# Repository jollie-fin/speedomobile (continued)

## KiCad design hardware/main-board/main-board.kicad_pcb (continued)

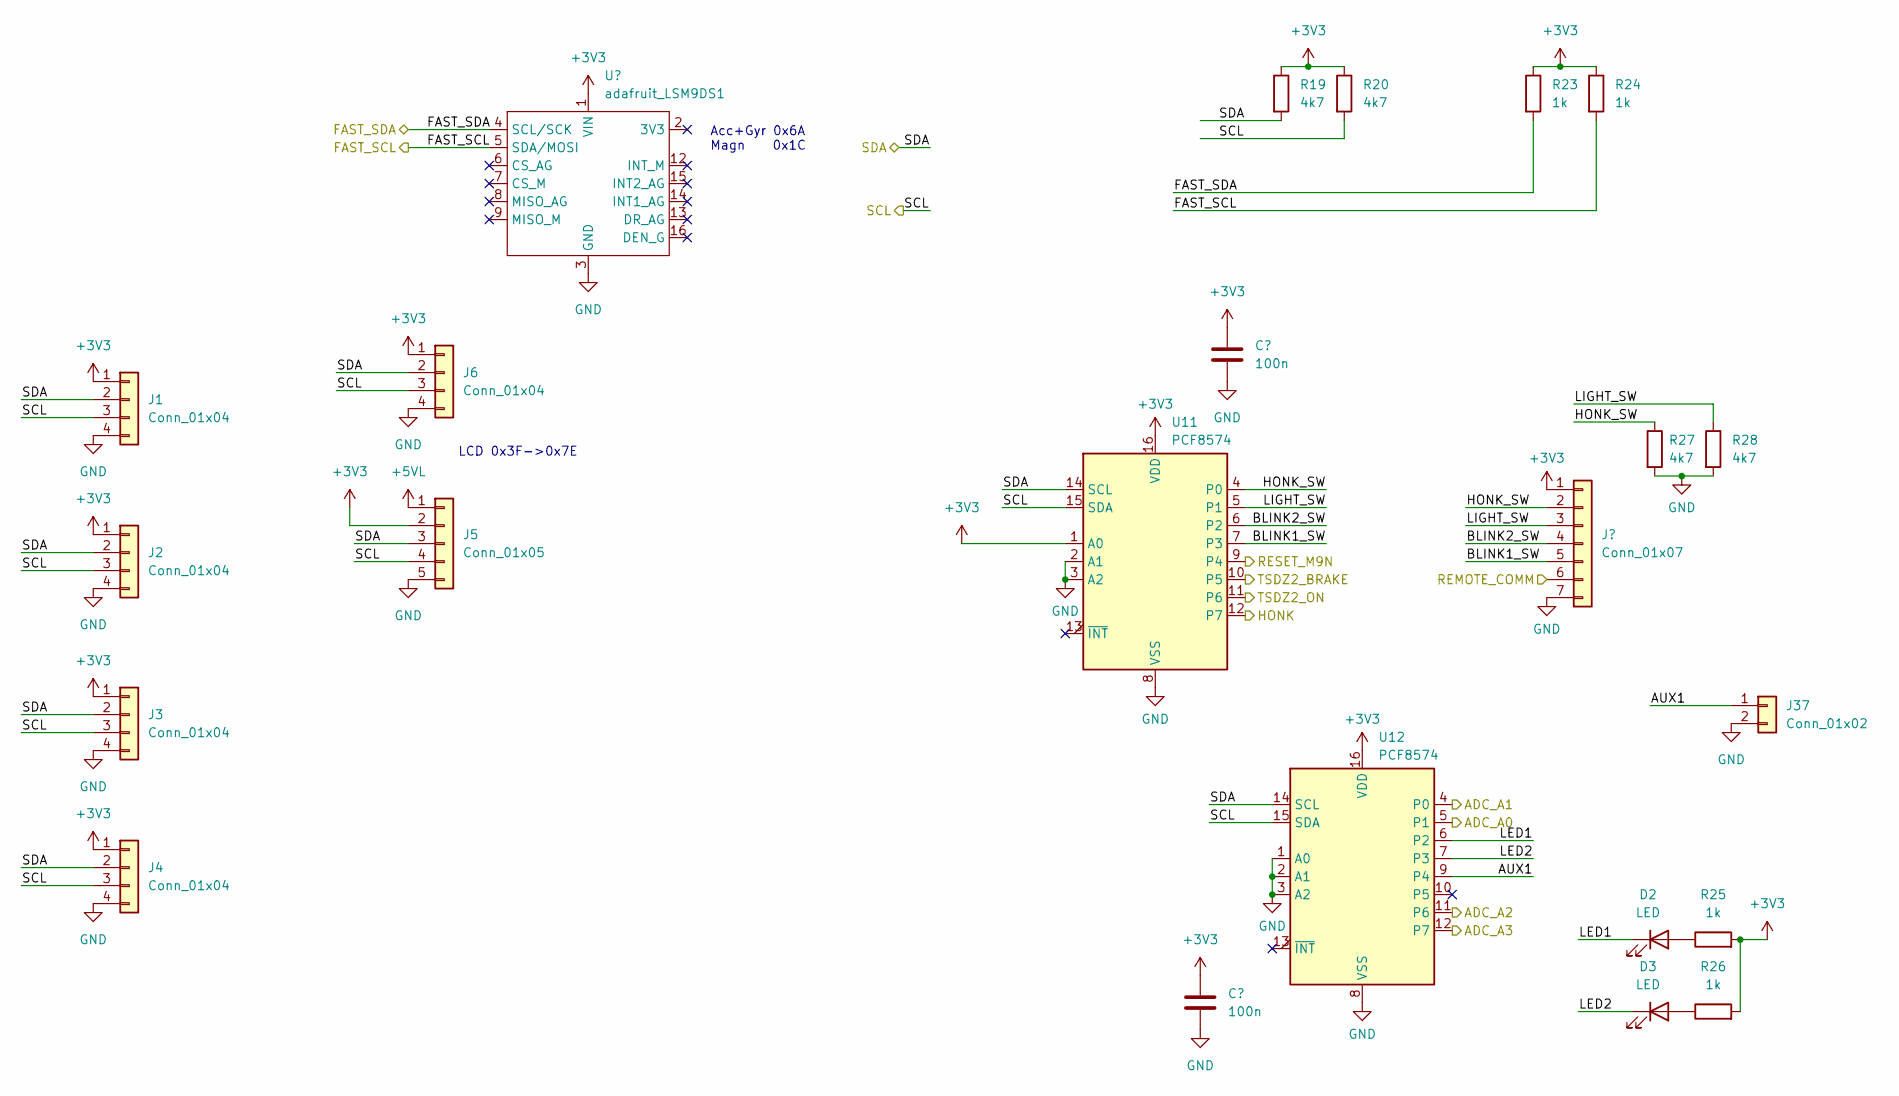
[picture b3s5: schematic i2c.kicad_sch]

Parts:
C21, C22: 100n; C_1206_3216Metric; mouser 80-C1206C104K5R
D2: LED; LED_1206_3216Metric; mouser 710-156120RS75300
D3: LED; LED_1206_3216Metric; mouser 710-156120VS75000
J1, J2, J3, J4, J6: Conn_01x04; JST_XH_B4B-XH-A_1x04_P2.50mm_Vertical
J5: Conn_01x05; JST_XH_B5B-XH-A_1x05_P2.50mm_Vertical
J7: Conn_01x07; JST_XH_B7B-XH-A_1x07_P2.50mm_Vertical
J37: Conn_01x02; JST_XH_B2B-XH-A_1x02_P2.50mm_Vertical
R19, R20, R27, R28: 4k7; R_1206_3216Metric; mouser 791-WR12X4701FTL
R23, R24, R25, R26: 1k; R_1206_3216Metric; mouser 603-AC1206FR-101KL
U9: adafruit_LSM9DS1; lsm9ds1_wo_holes
U11, U12: PCF8574; SOIC-16W_7.5x10.3mm_P1.27mm; mouser 771-PCF8574ATD-T

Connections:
+3V3: C21.1, C22.1, J1.1, J2.1, J3.1, J4.1, J5.2, J6.1, J7.1, R19.1, R20.1, R23.1, R24.1, R25.2, R26.2, U9.1 (VIN), U11.1 (A0), U11.16 (VDD), U12.16 (VDD); also elsewhere on the board
+5VL: J5.1; also elsewhere on the board
/ADC_A0: U12.5 (P1); also elsewhere on the board
/ADC_A1: U12.4 (P0); also elsewhere on the board
/ADC_A2: U12.11 (P6); also elsewhere on the board
/ADC_A3: U12.12 (P7); also elsewhere on the board
/FAST_SCL: R24.2, U9.5 (SDA/MOSI); also elsewhere on the board
/FAST_SDA: R23.2, U9.4 (SCL/SCK); also elsewhere on the board
/HONK: U11.12 (P7); also elsewhere on the board
/I2C devices/AUX1: J37.1, U12.9 (P4)
/I2C devices/LED1: D2.1 (K), U12.6 (P2)
/I2C devices/LED2: D3.1 (K), U12.7 (P3)
/RESET_M9N: U11.9 (P4); also elsewhere on the board
/SCL: J1.3, J2.3, J3.3, J4.3, J5.4, J6.3, R20.2, U11.15 (SDA), U12.15 (SDA); also elsewhere on the board
/SDA: J1.2, J2.2, J3.2, J4.2, J5.3, J6.2, R19.2, U11.14 (SCL), U12.14 (SCL); also elsewhere on the board
/TSDZ2_BRAKE: U11.10 (P5); also elsewhere on the board
/TSDZ2_ON: U11.11 (P6); also elsewhere on the board
GND: C21.2, C22.2, J1.4, J2.4, J3.4, J4.4, J5.5, J6.4, J7.7, J37.2, R27.2, R28.2, U9.3 (GND), U11.2 (A1), U11.3 (A2), U11.8 (VSS), U12.1 (A0), U12.2 (A1), U12.3 (A2), U12.8 (VSS); also elsewhere on the board
unnamed: D2.2 (A), R25.1
unnamed: D3.2 (A), R26.1

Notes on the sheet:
LCD 0x3F->0x7E
Acc+Gyr 0x6A Magn 0x1C

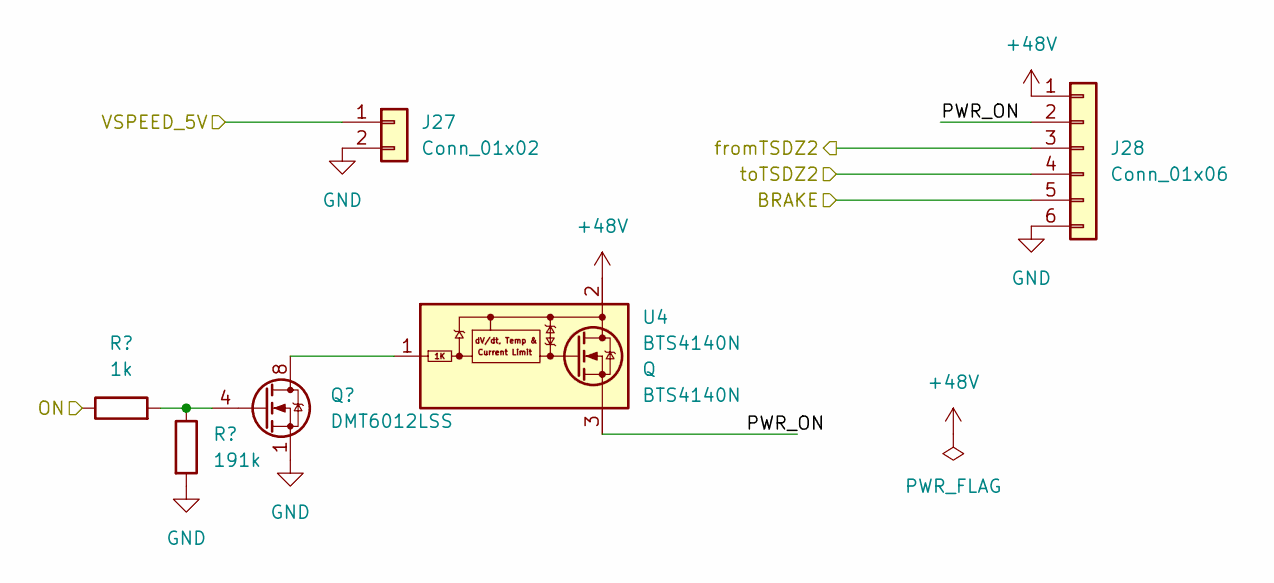
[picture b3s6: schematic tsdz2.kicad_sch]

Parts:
J27: Conn_01x02; JST_XH_B2B-XH-A_1x02_P2.50mm_Vertical
J28: Conn_01x06; JST_XH_B6B-XH-A_1x06_P2.50mm_Vertical
Q2: DMT6012LSS; SOIC-8_3.9x4.9mm_P1.27mm; mouser 621-DMT6012LSS-13
R5: 1k; R_1206_3216Metric; mouser 603-AC1206FR-101KL
R6: 191k; R_1206_3216Metric; mouser 660-RK73H2BTTD1913F
U4: BTS4140N; SOT-223; mouser 726-BTS4140N

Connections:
+48V: J28.1, U4.2 (D), U4.4 (D); also elsewhere on the board
/TSDZ2_BRAKE_5V: J28.5; also elsewhere on the board
/TSDZ2_ON_5V: R5.1; also elsewhere on the board
/TSDZ2_RX_5V: J28.3; also elsewhere on the board
/TSDZ2_TX_5V: J28.4; also elsewhere on the board
/VSPEED_5V: J27.1; also elsewhere on the board
/tsdz2/PWR_ON: J28.2, U4.3 (S)
GND: J27.2, J28.6, Q2.1 (S), Q2.2 (S), Q2.3 (S), R6.2; also elsewhere on the board
unnamed: Q2.4 (G), R5.2, R6.1
unnamed: Q2.5 (D), Q2.6 (D), Q2.7 (D), Q2.8 (D), U4.1 (G)

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
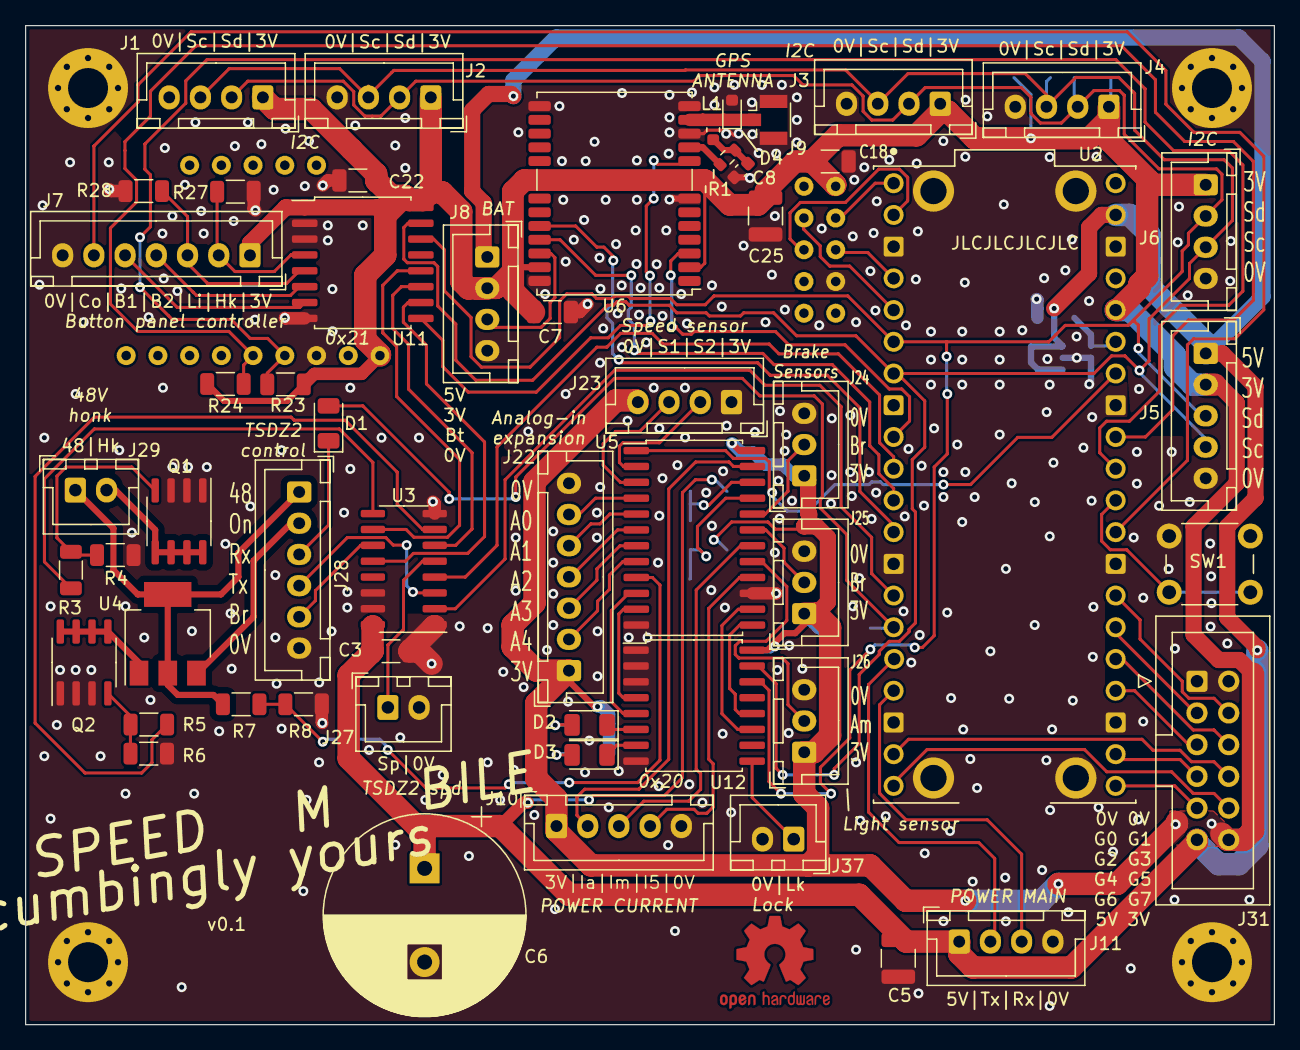
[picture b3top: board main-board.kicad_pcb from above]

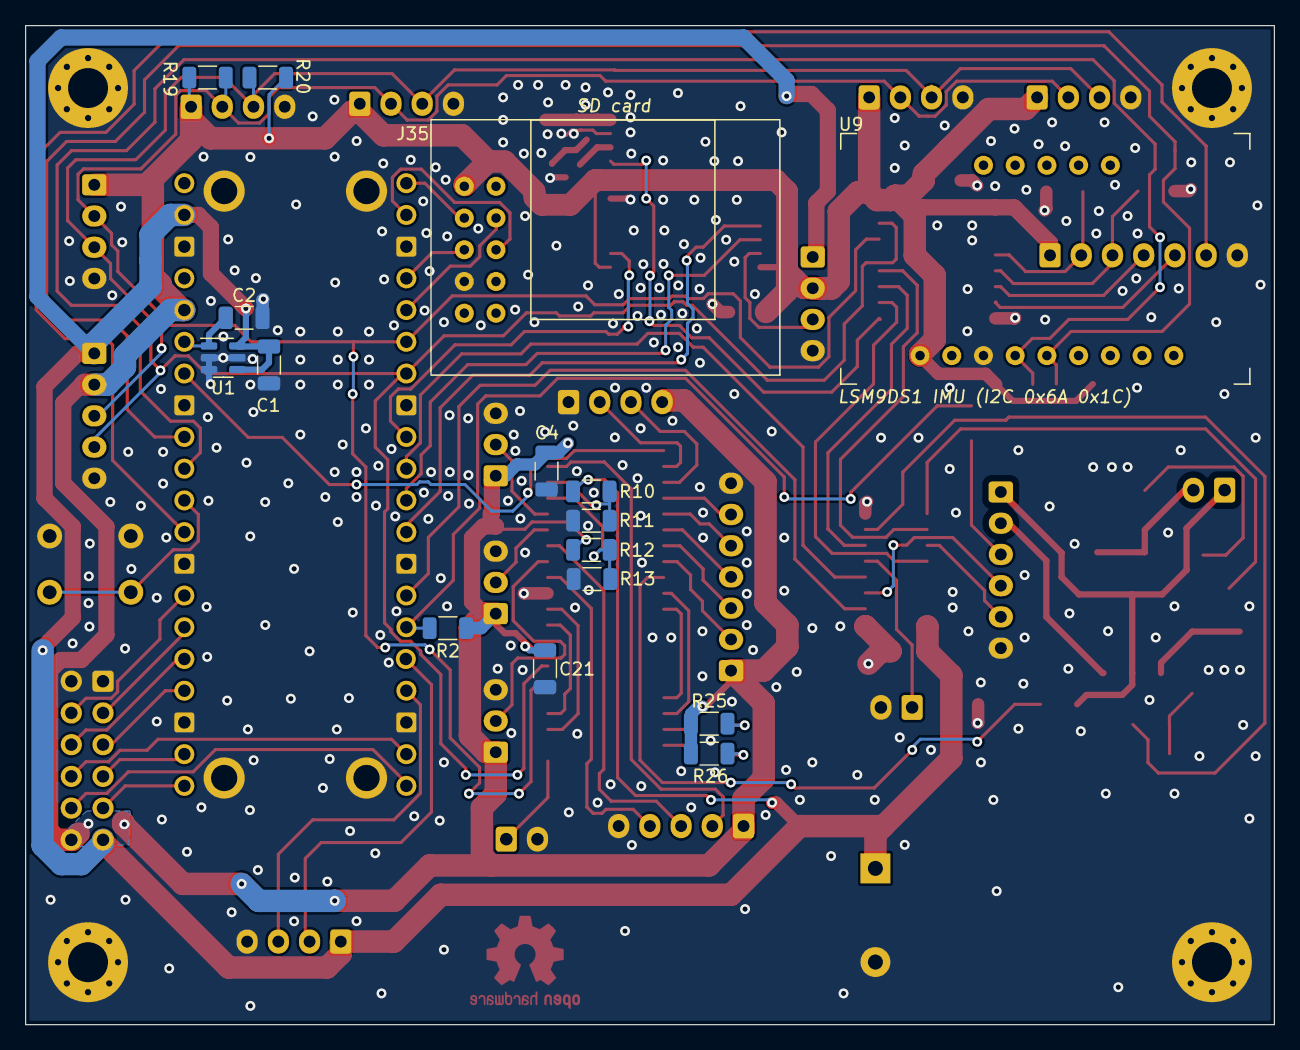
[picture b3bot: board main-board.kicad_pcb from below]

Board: 2 copper layers, 100.0 x 80.0 mm, 76 parts (20 on the bottom side), 80 nets.

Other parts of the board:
C7: 1u; C_1206_3216Metric
C8: 100n; C_0603_1608Metric
J8: Conn_01x04; JST_XH_B4B-XH-A_1x04_P2.50mm_Vertical
J22: Conn_01x07; JST_XH_B7B-XH-A_1x07_P2.50mm_Vertical
R1: 20; R_0603_1608Metric
U6: NEO-M9N; ublox_NEO

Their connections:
+3V3: C7.1, J8.2, J22.1, U6.2 (D_SEL), U6.23 (VCC); also elsewhere on the board
+5VL: J8.1; also elsewhere on the board
/GPS/RF_GPS: U6.11 (RF_IN); also elsewhere on the board
/GPS_RX: U6.20 (TXD/SPI_MISO); also elsewhere on the board
/GPS_TX: U6.21 (RXD/SPI_MOSI); also elsewhere on the board
/PPS: U6.3 (TIMEPULSE); also elsewhere on the board
/RESET_M9N: U6.8 (~RESET); also elsewhere on the board
GND: C7.2, C8.2, J8.4, J22.7, U6.7 (VDD_USB), U6.10 (GND), U6.12 (GND), U6.13 (GND), U6.24 (GND); also elsewhere on the board
unnamed 62: C8.1, R1.2; also elsewhere on the board
unnamed: J8.3, U6.22 (V_BCKP)
unnamed: R1.1, U6.9 (VCC_RF)

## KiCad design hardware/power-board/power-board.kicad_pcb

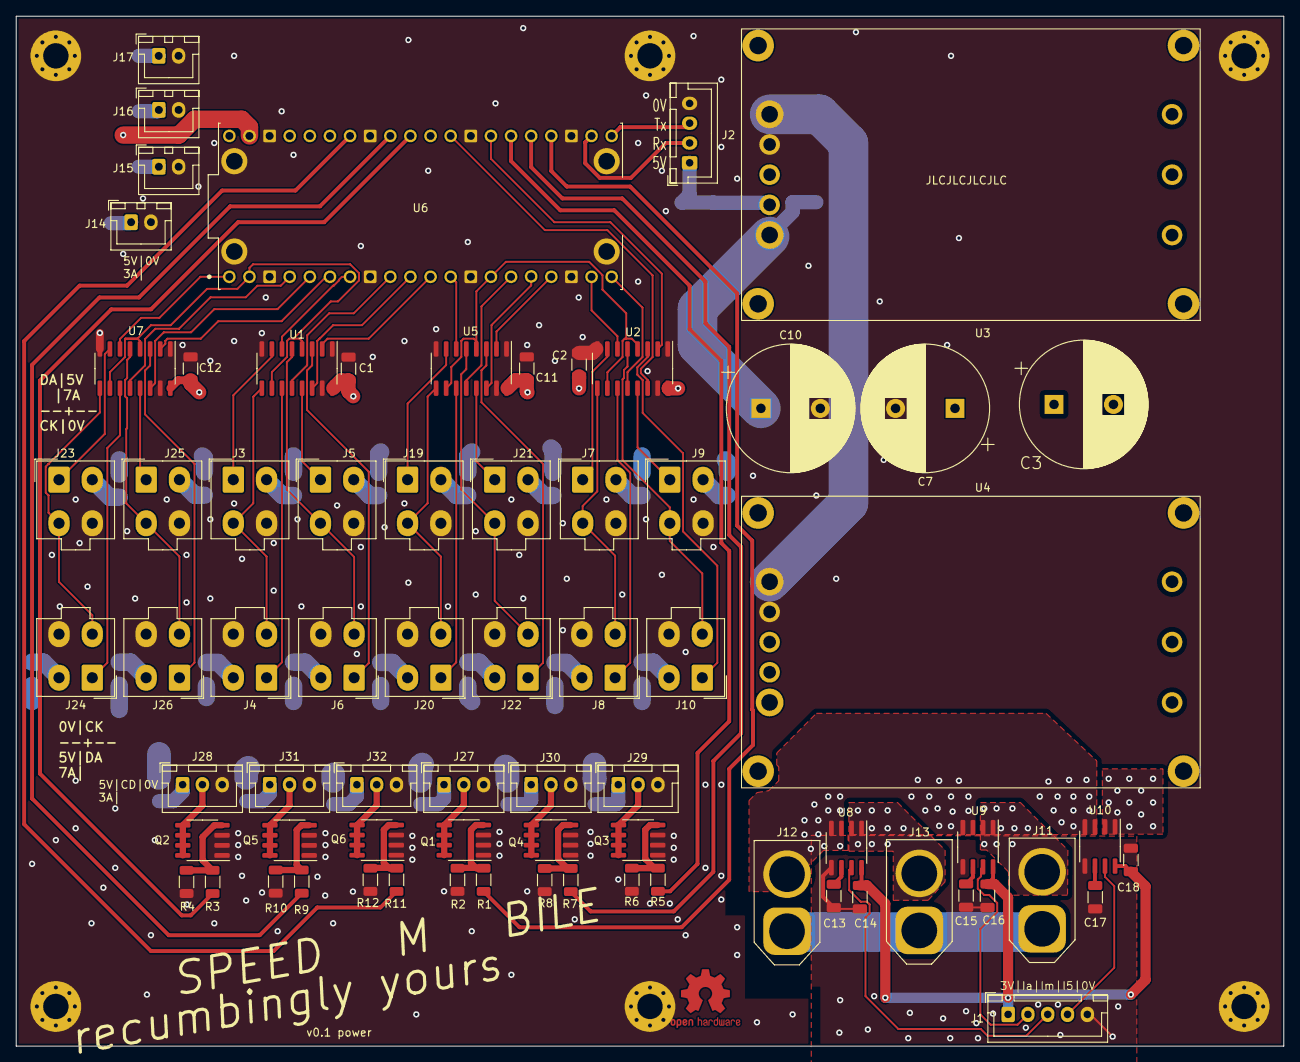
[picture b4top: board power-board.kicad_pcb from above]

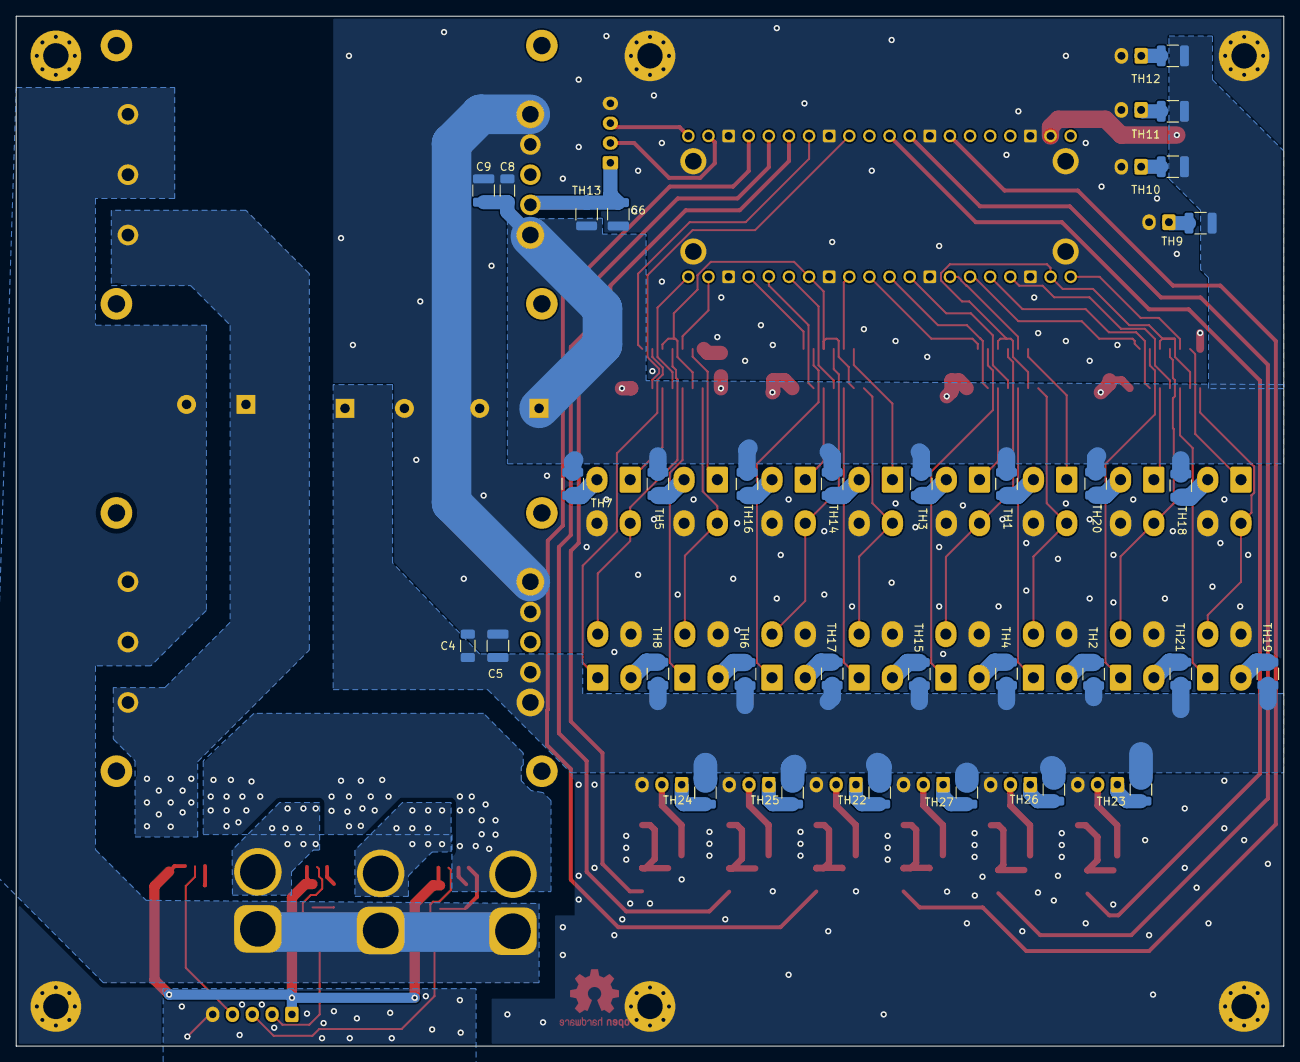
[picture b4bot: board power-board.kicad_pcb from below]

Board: 2 copper layers, 160.0 x 130.0 mm, 111 parts (38 on the bottom side), 105 nets.

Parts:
C1, C2, C11, C12: 100n; C_1206_3216Metric
C3, C7, C10: 220u; CP_Radial_D16.0mm_P7.50mm
C4, C8, C13, C14, C15, C16, C17, C18: 1u; C_1206_3216Metric
C5, C6, C9: 22u; C_1210_3225Metric
H1, H2, H3, H4, H5, H6: MountingHole_Pad; MountingHole_3.2mm_M3_Pad_Via
J1: JST_XH; JST_XH_B5B-XH-A_1x05_P2.50mm_Vertical
J2: JST_XH; JST_XH_B4B-XH-A_1x04_P2.50mm_Vertical
J3, J4, J5, J6, J7, J8, J9, J10, J19, J20, J21, J22, J23, J24, J25, J26: minifit; Molex_Mini-Fit_Jr_5566-04A_2x02_P4.20mm_Vertical
J11, J13: Conn_01x02; AMASS_XT60-F_1x02_P7.20mm_Vertical
J12: Conn_01x02; AMASS_XT60-M_1x02_P7.20mm_Vertical
J14, J15, J16, J17: Conn_01x02; JST_XH_B2B-XH-A_1x02_P2.50mm_Vertical
J27, J28, J29, J30, J31, J32: Conn_01x03; JST_XH_B3B-XH-A_1x03_P2.50mm_Vertical
Q1, Q2, Q3, Q4, Q5, Q6: DMT6012LSS; SOIC-8_3.9x4.9mm_P1.27mm
R1, R3, R5, R7, R9, R11: 1k; R_1206_3216Metric
R2, R4, R6, R8, R10, R12: 191k; R_1206_3216Metric
SYMB1: OSHW; OSHW-Logo2_9.8x8mm_Mask
TH1, TH2, TH3, TH4, TH5, TH6, TH7, TH8, TH14, TH15, TH16, TH17, TH18, TH19, TH20, TH21: 7,5A; R_1210_3225Metric
TH9, TH10, TH11, TH12, TH13, TH22, TH23, TH24, TH25, TH26, TH27: 3A; R_1210_3225Metric
U1, U2, U5, U7: 74AHCT367; SOIC-16_3.9x9.9mm_P1.27mm
U3, U4: VCB48_QBO-200WR3-N; VCB48
U6: SC0918; MODULE_SC0918
U8, U9, U10: MCS1802; SOIC-8_3.9x4.9mm_P1.27mm

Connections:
+3.3VA: C14.1, C16.1, C18.1, J1.1, U8.8 (VCC), U9.8 (VCC), U10.8 (VCC)
+5V: C1.2, C2.2, C8.1, C9.1, C10.1, C11.2, C12.2, TH1.2, TH3.2, TH5.2, TH7.2, TH9.1, TH10.1, TH11.1, TH12.1, TH13.1, TH14.2, TH16.2, TH18.2, TH20.2, U1.16 (VCC), U2.16 (VCC), U3.8 (+VOUT), U5.16 (VCC), U6.39 (VSYS), U7.16 (VCC)
+5VL: C6.1, J2.1, TH13.2, U3.7 (Sense+)
+5VP: C4.1, C5.1, C7.1, TH2.2, TH4.2, TH6.2, TH8.2, TH15.2, TH17.2, TH19.2, TH21.2, TH22.2, TH23.2, TH24.2, TH25.2, TH26.2, TH27.2, U4.7 (Sense+), U4.8 (+VOUT)
+BATT: J12.2, U8.3 (IP-), U8.4 (IP-), U9.3 (IP-), U9.4 (IP-), U10.3 (IP-), U10.4 (IP-)
-BATT: C3.2, J11.1, J12.1, J13.1, U3.2 (ON/~OFF), U3.3 (-VIN), U4.2 (ON/~OFF), U4.3 (-VIN)
/UARTRX: J2.2, U6.22 (UART0RX/I2C0SCL/SPI0Cs/GP17)
/UARTTX: J2.3, U6.21 (UART0TX/I2C0SDA/SPI0RX/GP16)
/ledribbon/MOSI0: U6.1 (UART0TX/I2C0SDA/SPI0RX/GP00), U7.6 (I3)
/ledribbon/MOSI1: U6.4 (I2C1SDA/SPI0CK/GP02), U7.12 (I5)
/ledribbon/MOSI2: U6.5 (I2C1SCL/SPI0TX/GP03), U7.14 (I6)
/ledribbon/MOSI3: U6.6 (UART1TX/I2C0SDA/SPI0RX/GP04), U7.2 (I1)
/ledribbon/MOSI4: U1.6 (I3), U6.7 (UART1RX/I2C0SCL/SPI0Cs/GP05)
/ledribbon/MOSI5: U1.12 (I5), U6.9 (I2C1SDA/SPI0CK/GP06)
/ledribbon/MOSI6: U1.14 (I6), U6.10 (I2C1SCL/SPI0TX/GP07)
/ledribbon/MOSI7: U1.2 (I1), U6.11 (UART1TX/I2C0SDA/SPI1RX/GP08)
/ledribbon/MOSI8: U5.6 (I3), U6.12 (UART1RX/I2C0SCL/SPI1Cs/GP09)
/ledribbon/MOSI9: U5.12 (I5), U6.15 (I2C1SCL/SPI1TX/GP11)
/ledribbon/MOSI10: U5.14 (I6), U6.16 (UART0TX/I2C0SDA/SPI1RX/GP12)
/ledribbon/MOSI11: U5.2 (I1), U6.17 (UART0RX/I2C0SCL/SPI1Cs/GP13)
/ledribbon/MOSI12: U2.6 (I3), U6.19 (I2C1SDA/SPI1CK/GP14)
/ledribbon/MOSI13: U2.12 (I5), U6.20 (I2C1SCL/SPI1TX/GP15)
/ledribbon/MOSI14: U2.14 (I6), U6.29 (GP22)
/ledribbon/MOSI15: U2.2 (I1), U6.27 (I2C0SCL/GP21)
/ledribbon/PWM0: R5.1, U6.26 (I2C0SDA/GP20)
/ledribbon/PWM1: R7.1, U6.25 (I2C1SCL/SPI0TX/GP19)
/ledribbon/PWM2: R1.1, U6.24 (I2C1SDA/SPI0CK/GP18)
/ledribbon/PWM3: R11.1, U6.34 (ADC2/GP28)
/ledribbon/PWM4: R9.1, U6.32 (I2C1SCL/ADC1/GP27)
/ledribbon/PWM5: R3.1, U6.31 (I2C1SDA/ADC0/GP26)
/ledribbon/SCK0-7: U1.4 (I2), U1.10 (I4), U6.2 (UART0RX/I2C0SCL/SPI0Cs/GP01), U7.4 (I2), U7.10 (I4)
/ledribbon/SCK8-15: U2.4 (I2), U2.10 (I4), U5.4 (I2), U5.10 (I4), U6.14 (I2C1SDA/SPI1CK/GP10)
/power/Dcdc: C3.1, U3.1 (+VIN), U4.1 (+VIN), U10.1 (IP+), U10.2 (IP+)
/power/I5V: J1.4, U10.7 (VIOUT)
/power/Iaux: J1.2, U9.7 (VIOUT)
/power/Imotor: J1.3, U8.7 (VIOUT)
/power/Motor: J13.2, U8.1 (IP+), U8.2 (IP+)
/power/PWR1: J14.1, TH9.2
/power/PWR2: J15.1, TH10.2
/power/PWR3: J16.1, TH11.2
/power/PWR4: J17.1, TH12.2
/power/aux48v: J11.2, U9.1 (IP+), U9.2 (IP+)
GND: C1.1, C2.1, C4.2, C5.2, C6.2, C7.2, C8.2, C9.2, C10.2, C11.1, C12.1, H1.1, H2.1, H3.1, H4.1, H5.1, H6.1, J2.4, J3.4, J4.4, J5.4, J6.4, J7.4, J8.4, J9.4, J10.4, J14.2, J15.2, J16.2, J17.2, J19.4, J20.4, J21.4, J22.4, J23.4, J24.4, J25.4, J26.4, J27.3, J28.3, J29.3, J30.3, J31.3, J32.3, Q1.1 (S), Q1.2 (S), Q1.3 (S), Q2.1 (S), Q2.2 (S), Q2.3 (S), Q3.1 (S), Q3.2 (S), Q3.3 (S), Q4.1 (S), Q4.2 (S), Q4.3 (S), Q5.1 (S), Q5.2 (S), Q5.3 (S), Q6.1 (S), Q6.2 (S), Q6.3 (S), R2.2, R4.2, R6.2, R8.2, R10.2, R12.2, U1.1 (OEa), U1.8 (GND), U1.15 (OEb), U2.1 (OEa), U2.8 (GND), U2.15 (OEb), U3.4 (-VOUT), U3.5 (Sense-), U4.4 (-VOUT), U4.5 (Sense-), U5.1 (OEa), U5.8 (GND), U5.15 (OEb), U6.3 (GND), U6.8 (GND), U6.13 (GND), U6.18 (GND), U6.23 (GND), U6.28 (GND), U6.33 (AGND), U6.38 (GND), U6.M1 (GND), U6.M2 (GND), U6.M3 (GND), U6.M4 (GND), U7.1 (OEa), U7.8 (GND), U7.15 (OEb)
GNDA: C13.2, C14.2, C15.2, C16.2, C17.2, C18.2, J1.5, U8.5 (GND), U9.5 (GND), U10.5 (GND)
unnamed: J3.1, U1.7 (O3a)
unnamed: J3.2, TH1.1
unnamed: J3.3, J4.3, U1.9 (O4a)
unnamed: J4.1, U1.11 (O5b)
unnamed: J4.2, TH2.1
unnamed: J5.1, U1.13 (O6b)
unnamed: J5.2, TH3.1
unnamed: J5.3, J6.3, U1.5 (O2a)
unnamed: J6.1, U1.3 (O1a)
unnamed: J6.2, TH4.1
unnamed: J7.1, U2.7 (O3a)
unnamed: J7.2, TH5.1
unnamed: J7.3, J8.3, U2.9 (O4a)
unnamed: J8.1, U2.11 (O5b)
unnamed: J8.2, TH6.1
unnamed: J9.1, U2.13 (O6b)
unnamed: J9.2, TH7.1
unnamed: J10.1, U2.3 (O1a)
unnamed: J10.2, TH8.1
unnamed: J9.3, J10.3, U2.5 (O2a)
unnamed: J19.1, U5.7 (O3a)
unnamed: J19.2, TH14.1
unnamed: J19.3, J20.3, U5.9 (O4a)
unnamed: J20.1, U5.11 (O5b)
unnamed: J20.2, TH15.1
unnamed: J21.1, U5.13 (O6b)
unnamed: J21.2, TH16.1
unnamed: J21.3, J22.3, U5.5 (O2a)
unnamed: J22.1, U5.3 (O1a)
unnamed: J22.2, TH17.1
unnamed: J23.1, U7.7 (O3a)
unnamed: J23.2, TH18.1
unnamed: J23.3, J24.3, U7.9 (O4a)
unnamed: J24.1, U7.11 (O5b)
unnamed: J24.2, TH19.1
unnamed: J25.1, U7.13 (O6b)
unnamed: J25.2, TH20.1
unnamed: J25.3, J26.3, U7.5 (O2a)
unnamed: J26.1, U7.3 (O1a)
unnamed: J26.2, TH21.1
unnamed: J27.1, TH22.1
unnamed: J27.2, Q1.5 (D), Q1.6 (D), Q1.7 (D), Q1.8 (D)
unnamed: J28.1, TH23.1
unnamed: J28.2, Q2.5 (D), Q2.6 (D), Q2.7 (D), Q2.8 (D)
unnamed: J29.1, TH24.1
unnamed: J29.2, Q3.5 (D), Q3.6 (D), Q3.7 (D), Q3.8 (D)
unnamed: J30.1, TH25.1
unnamed: J30.2, Q4.5 (D), Q4.6 (D), Q4.7 (D), Q4.8 (D)
unnamed: J31.1, TH26.1
unnamed: J31.2, Q5.5 (D), Q5.6 (D), Q5.7 (D), Q5.8 (D)
unnamed: J32.1, TH27.1
unnamed: J32.2, Q6.5 (D), Q6.6 (D), Q6.7 (D), Q6.8 (D)
unnamed: Q1.4 (G), R1.2, R2.1
unnamed: Q2.4 (G), R3.2, R4.1
unnamed: Q3.4 (G), R5.2, R6.1
unnamed: Q4.4 (G), R7.2, R8.1
unnamed: Q5.4 (G), R9.2, R10.1
unnamed: Q6.4 (G), R11.2, R12.1
unnamed: C13.1, U8.6 (FILTER)
unnamed: C15.1, U9.6 (FILTER)
unnamed: C17.1, U10.6 (FILTER)

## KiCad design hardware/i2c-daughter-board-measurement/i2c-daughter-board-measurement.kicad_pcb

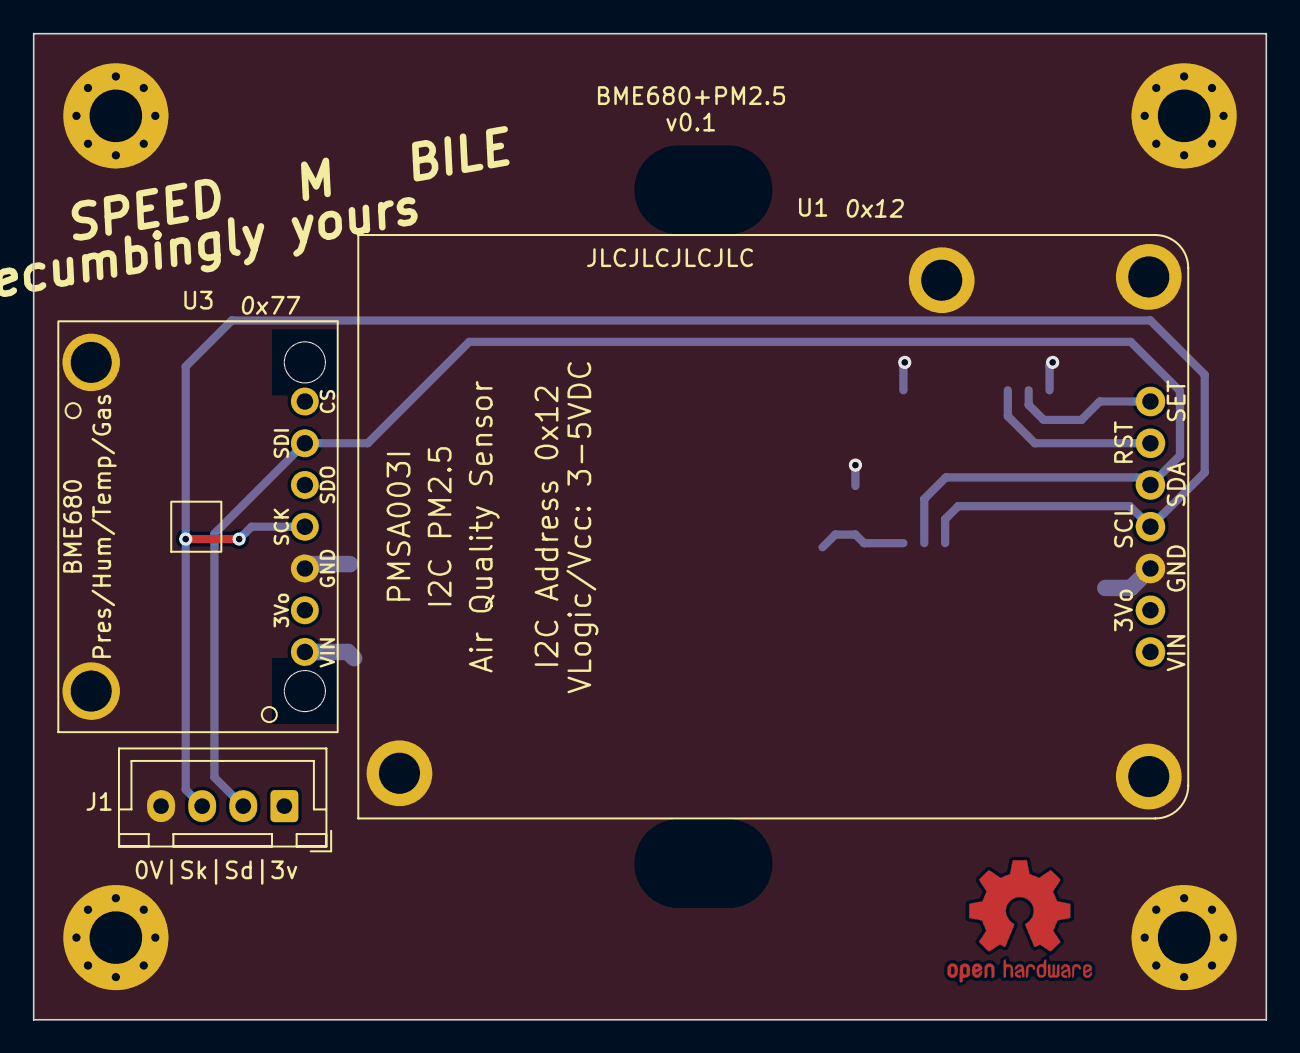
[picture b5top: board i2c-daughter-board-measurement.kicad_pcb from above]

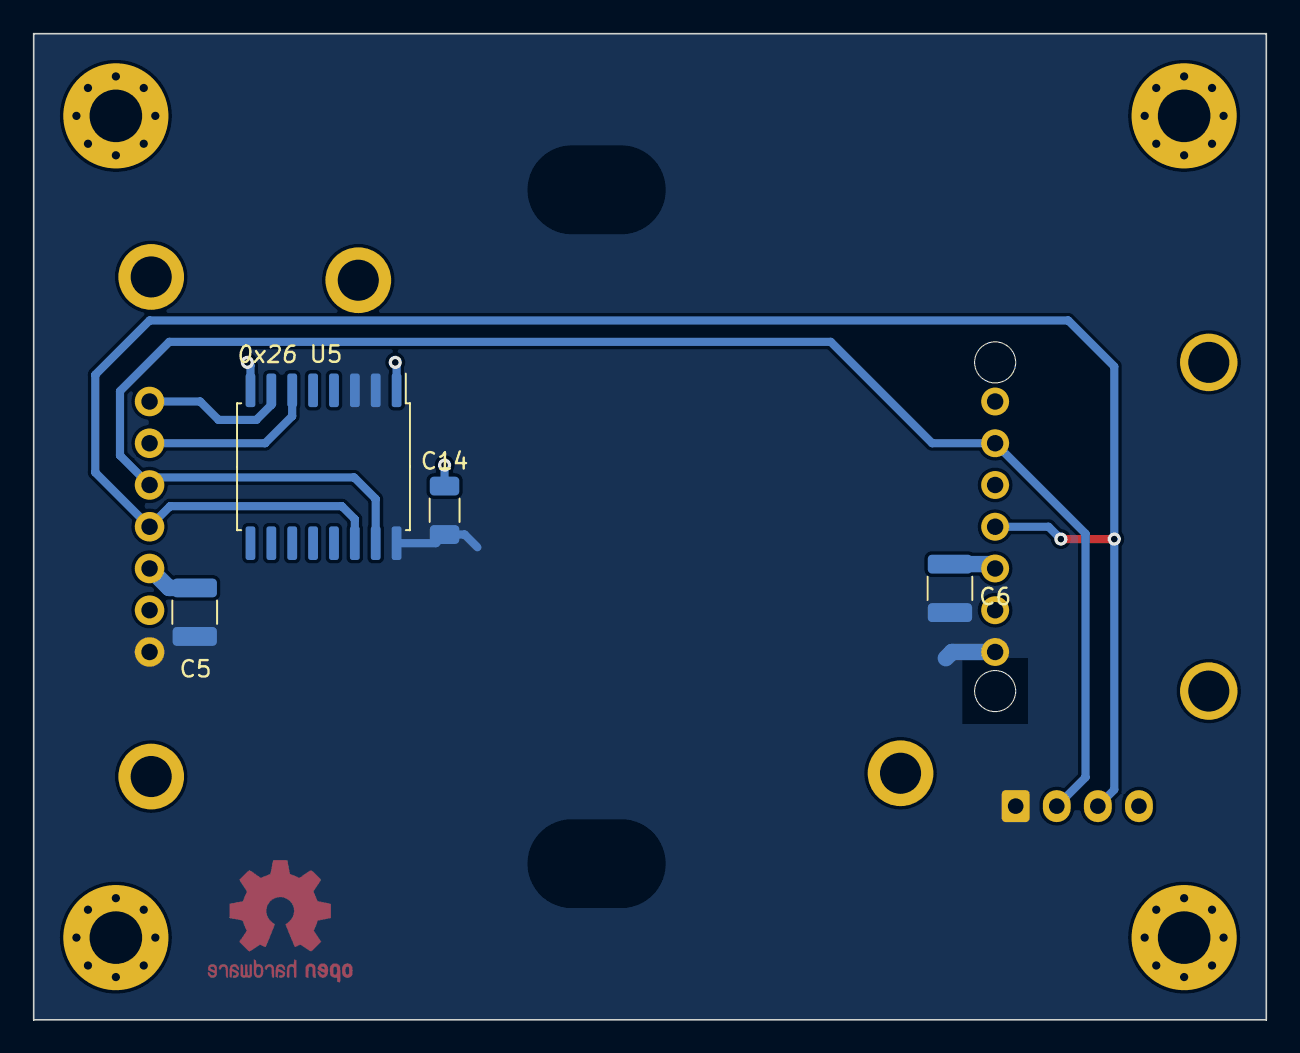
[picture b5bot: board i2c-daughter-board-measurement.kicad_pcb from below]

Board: 2 copper layers, 75.0 x 60.0 mm, 12 parts (4 on the bottom side), 6 nets.

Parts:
C5, C6: 22u; C_1210_3225Metric
C14: 100n; C_1206_3216Metric
H1, H2, H3, H4: M3; MountingHole_3.2mm_M3_Pad_Via
J1: Conn_01x04; JST_XH_B4B-XH-A_1x04_P2.50mm_Vertical
SYMB1: OSHW; OSHW-Logo2_9.8x8mm_Mask
U1: PMSA003I
U3: bme680
U5: PCF8574; SOIC-16W_7.5x10.3mm_P1.27mm

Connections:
+3V3: C5.1, C6.1, C14.1, J1.1, U1.1 (VCC), U3.1 (VCC), U5.2 (A1), U5.3 (A2), U5.16 (VDD)
/RST: U1.6 (RST), U5.6 (P2)
/SCL: J1.3, U1.4 (SCL), U3.4 (SCK/SCL), U5.14 (SCL)
/SDA: J1.2, U1.5 (SDA), U3.6 (SDA/SDI), U5.15 (SDA)
/SET: U1.7 (SET), U5.7 (P3)
GND: C5.2, C6.2, C14.2, H1.1, H2.1, H3.1, H4.1, J1.4, U1.3 (GND), U3.3 (GND), U5.1 (A0), U5.8 (VSS)

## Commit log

2024-02-07 molex2x2
2024-02-07 switching to 3v3 i2c
2024-02-09 JLCJLCJLCJLC
2024-02-11 2 layers!
2024-02-12 2 layer better ground plane
2024-02-13 Before flip
2024-02-18 before expansion
2024-02-26 Prepare for merging
2024-02-26 Prepare for merge
2024-02-27 before merge
2024-02-27 After merge
2024-02-27 Cleanup in hardware
2024-02-27 Forgotten library
2024-02-27 Fixed footprint
2024-02-27 Create LICENSE
2024-02-27 Updating images & 3d models
2024-02-27 Converting perspective files to jpg
2024-02-27 Renaming image files
2024-02-27 Improving README
2024-02-29 Adding blinkers
